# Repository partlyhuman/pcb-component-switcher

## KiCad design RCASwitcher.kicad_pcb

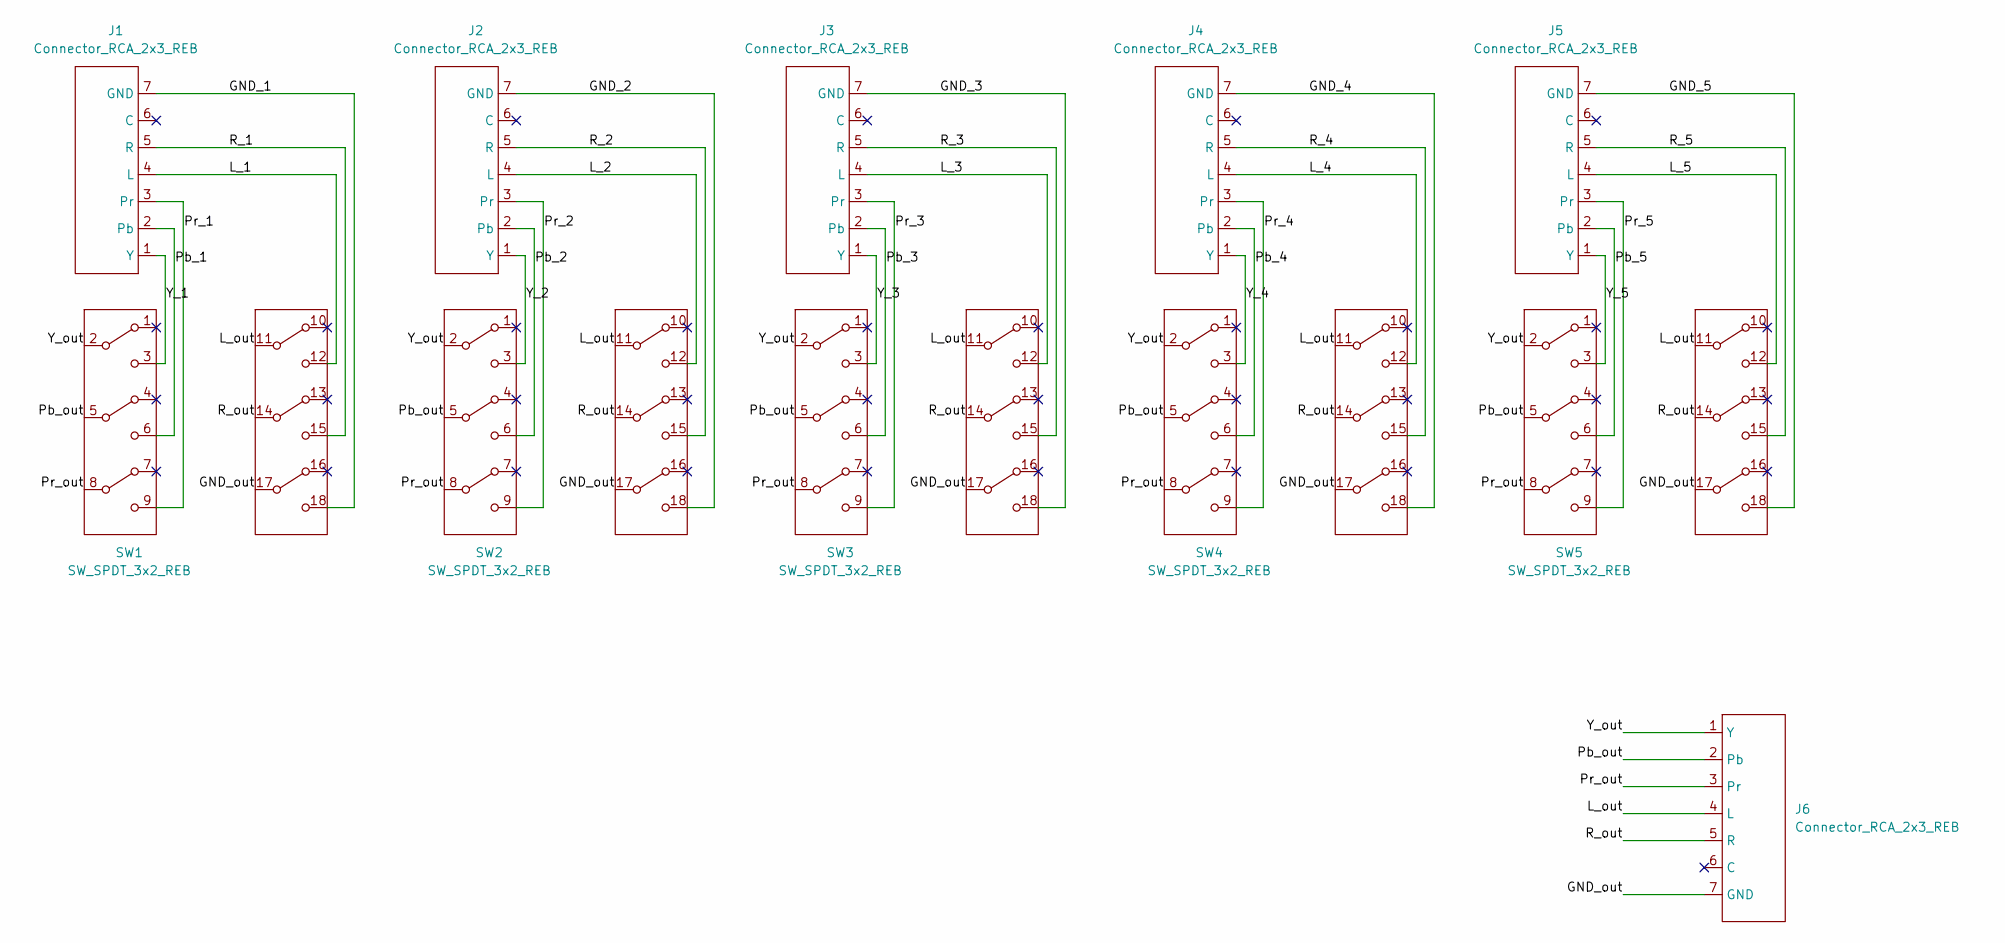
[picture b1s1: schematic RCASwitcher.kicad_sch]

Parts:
J1, J2, J3, J4, J5, J6: Connector_RCA_2x3_REB
SW1, SW2, SW3, SW4, SW5: SW_SPDT_3x2_REB

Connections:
/GND_1: J1.7 (GND), J1.8 (GND), J1.9 (GND), SW1.18 (C)
/GND_2: J2.7 (GND), J2.8 (GND), J2.9 (GND), SW2.18 (C)
/GND_3: J3.7 (GND), J3.8 (GND), J3.9 (GND), SW3.18 (C)
/GND_4: J4.7 (GND), J4.8 (GND), J4.9 (GND), SW4.18 (C)
/GND_5: J5.7 (GND), J5.8 (GND), J5.9 (GND), SW5.18 (C)
/GND_out: J6.7 (GND), J6.8 (GND), J6.9 (GND), SW1.17 (B), SW2.17 (B), SW3.17 (B), SW4.17 (B), SW5.17 (B)
/L_1: J1.4 (L), SW1.12 (C)
/L_2: J2.4 (L), SW2.12 (C)
/L_3: J3.4 (L), SW3.12 (C)
/L_4: J4.4 (L), SW4.12 (C)
/L_5: J5.4 (L), SW5.12 (C)
/L_out: J6.4 (L), SW1.11 (C), SW2.11 (C), SW3.11 (C), SW4.11 (C), SW5.11 (C)
/Pb_1: J1.2 (Pb), SW1.6 (C)
/Pb_2: J2.2 (Pb), SW2.6 (C)
/Pb_3: J3.2 (Pb), SW3.6 (C)
/Pb_4: J4.2 (Pb), SW4.6 (C)
/Pb_5: J5.2 (Pb), SW5.6 (C)
/Pb_out: J6.2 (Pb), SW1.5 (B), SW2.5 (B), SW3.5 (B), SW4.5 (B), SW5.5 (B)
/Pr_1: J1.3 (Pr), SW1.9 (C)
/Pr_2: J2.3 (Pr), SW2.9 (C)
/Pr_3: J3.3 (Pr), SW3.9 (C)
/Pr_4: J4.3 (Pr), SW4.9 (C)
/Pr_5: J5.3 (Pr), SW5.9 (C)
/Pr_out: J6.3 (Pr), SW1.8 (B), SW2.8 (B), SW3.8 (B), SW4.8 (B), SW5.8 (B)
/R_1: J1.5 (R), SW1.15 (C)
/R_2: J2.5 (R), SW2.15 (C)
/R_3: J3.5 (R), SW3.15 (C)
/R_4: J4.5 (R), SW4.15 (C)
/R_5: J5.5 (R), SW5.15 (C)
/R_out: J6.5 (R), SW1.14 (B), SW2.14 (B), SW3.14 (B), SW4.14 (B), SW5.14 (B)
/Y_1: J1.1 (Y), SW1.3 (C)
/Y_2: J2.1 (Y), SW2.3 (C)
/Y_3: J3.1 (Y), SW3.3 (C)
/Y_4: J4.1 (Y), SW4.3 (C)
/Y_5: J5.1 (Y), SW5.3 (C)
/Y_out: J6.1 (Y), SW1.2 (OA), SW2.2 (OA), SW3.2 (OA), SW4.2 (OA), SW5.2 (OA)

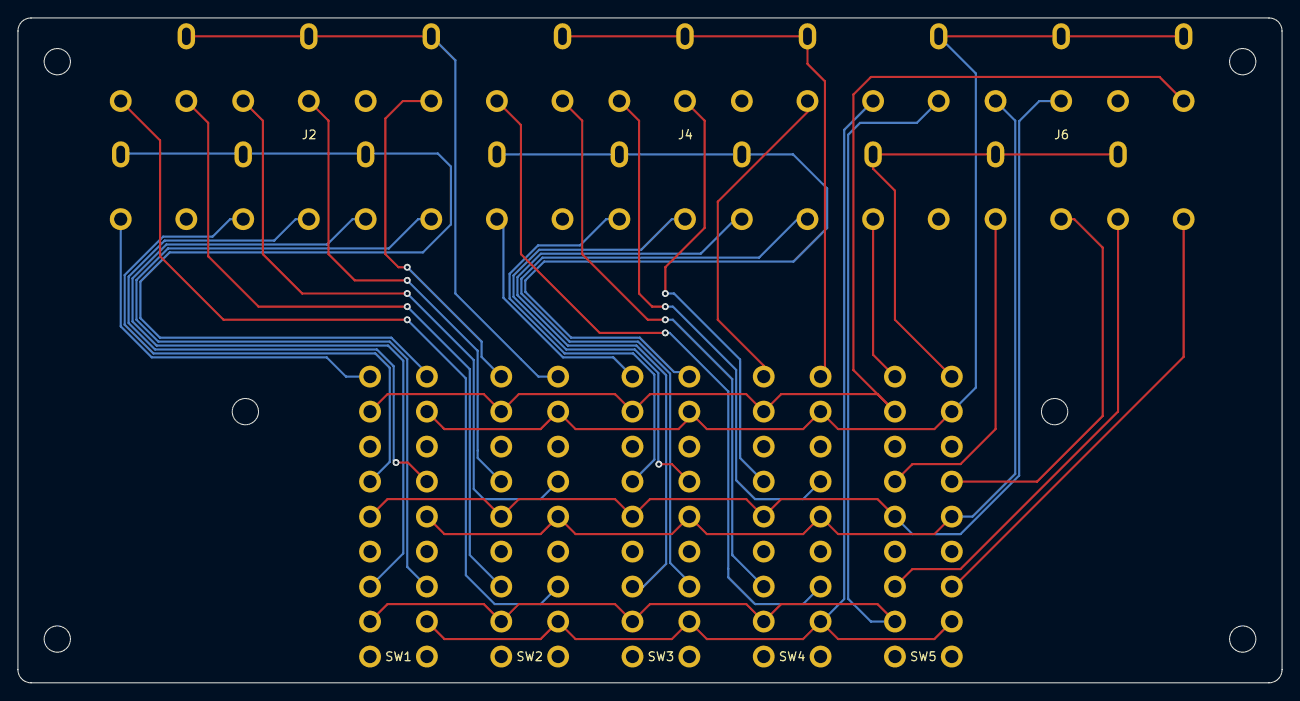
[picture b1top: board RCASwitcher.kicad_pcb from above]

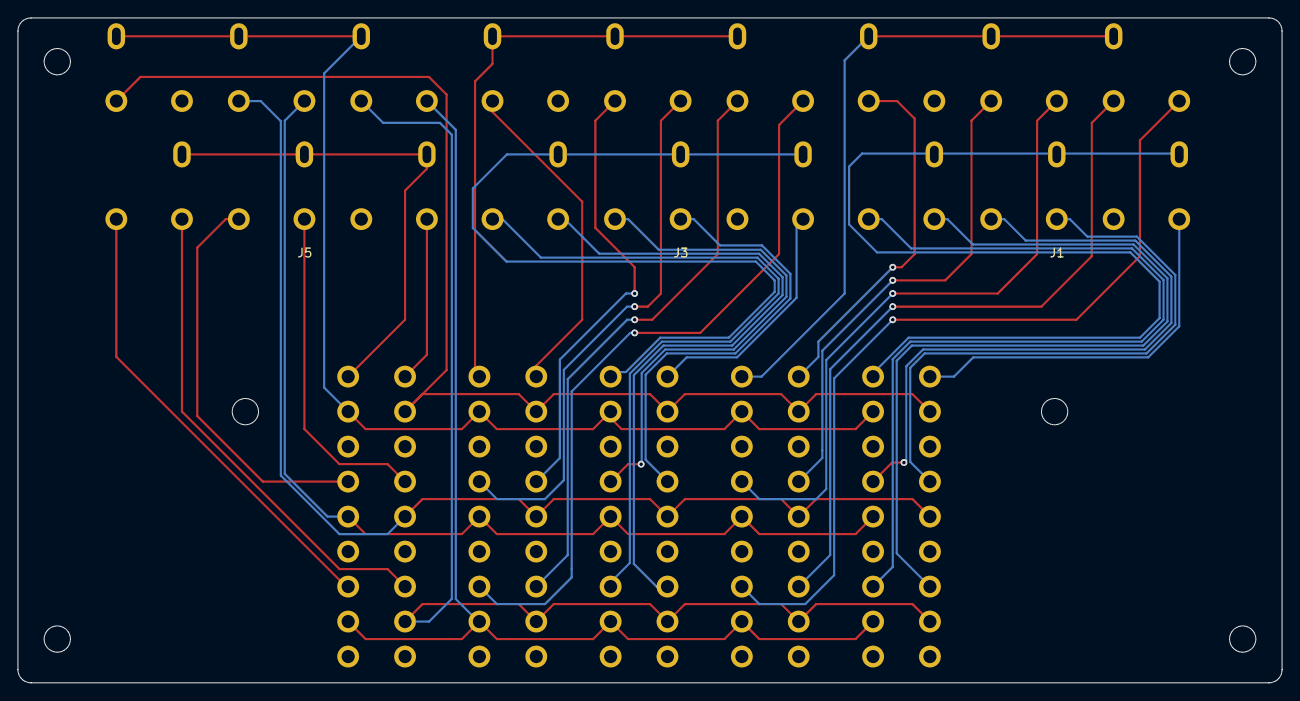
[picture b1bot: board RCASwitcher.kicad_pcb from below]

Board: 2 copper layers, 144.5 x 76.0 mm, 11 parts (3 on the bottom side), 36 nets.

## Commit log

2022-09-19 Removing ignored files, some layout
2022-09-19 finish hookups
2022-09-19 Name remaining nets for checking
2022-09-19 Adds notes, one big mistake with switch must fix
2022-09-20 Reversing which side gets connected, tested with hand soldering
2022-09-20 Expand board a little to add mount points
2022-12-02 Adds 3d model and gerbers for fabrication
2022-12-02 Adds STLs
2023-02-08 Nudge rows apart a little to fix overlap
2023-12-20 Split into RCA/VGA variants
